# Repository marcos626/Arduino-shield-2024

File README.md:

# Arduino-shield-2024
 Shield para arduino uno, curso de Laboratorio de Electrónica II

# Que es un shield?
La traducción literal sería "escudo", pero me parece más acertado el término "poncho" que suele utilizar el ing. Turra.

Son placas de expansión o extensión, que permiten agregar funcionalidad, en este caso a Arduino Uno. Son prácticos, porque se encastran o "enchufan" sin ninguna complicación, y puede apilarse más de un shield, uno encima de otro.

En la siguiente imagen, tomamos como ejemplo un shield fabricado por la empresa Seed Studio, llamado Base shield V2. 

Hay cientos de ejemplos, por ejemplo, los más populares:

https://randomnerdtutorials.com/25-arduino-shields/

## Diseño de un shield personalizado

En nuestro caso, vamos a diseñar un shield que nos permita utilizar:

* Sensor de corriente SCT-013
*Sensor de temperatura y humedad DHT-22
* Lector RFID  RC522
* Módulo ethernet Wiznet W5500
* Módulo bluetooth bt-06
* Puertos I2C para conectar, por ejemplo, un display LCD 16x2 con adaptador I2C
* Puertos digitales y analógicos

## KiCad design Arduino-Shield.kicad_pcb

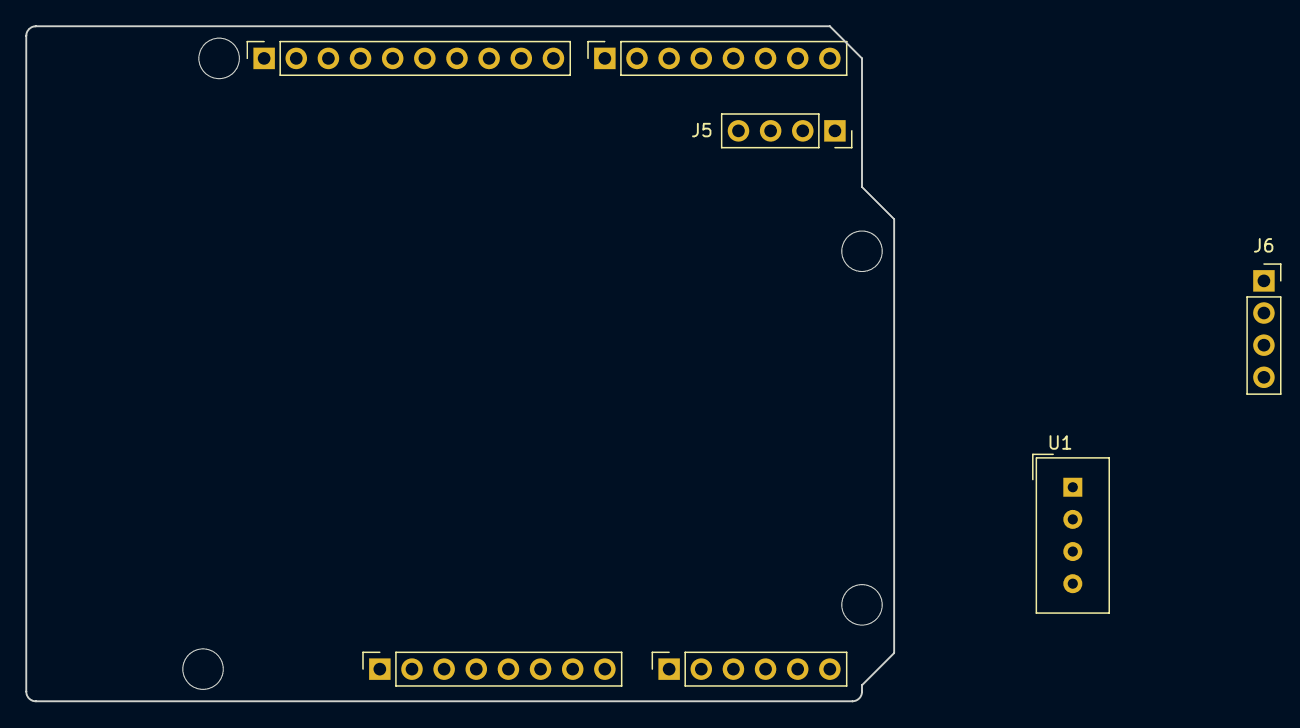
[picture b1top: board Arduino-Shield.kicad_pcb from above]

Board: 2 copper layers, 68.6 x 53.3 mm, 11 parts (0 on the bottom side), 6 nets, no tracks yet.

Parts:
J1: Power; PinSocket_1x08_P2.54mm_Vertical
J2: Digital/PWM; PinSocket_1x10_P2.54mm_Vertical
J3: Analog; PinSocket_1x06_P2.54mm_Vertical
J4: Digital/PWM; PinSocket_1x08_P2.54mm_Vertical
J5, J6: Conn_01x04_Pin; PinSocket_1x04_P2.54mm_Vertical
MH1, MH2, MH3, MH4: MountingHole_3.2mm
U1: DHT11; Aosong_DHT11_5.5x12.0_P2.54mm

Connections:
+5V: J1.5, J5.3
/RX/0: J4.8, J5.1
/SCL/A5: J2.1, J3.6
/SDA/A4: J2.2, J3.5
/TX/1: J4.7, J5.2
GND: J1.6, J1.7, J2.4, J5.4

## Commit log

2024-08-18 archivos de kicad
2024-08-18 cambios en título y descripción del esquema y placa
